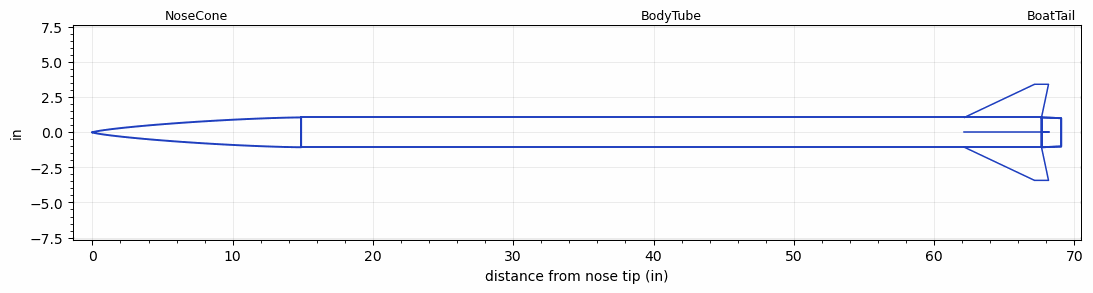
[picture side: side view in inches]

<RASAeroDocument>
 <FileVersion>2</FileVersion>
 <RocketDesign>
  <NoseCone>
   <Length>14.88</Length>
   <Diameter>2.125</Diameter>
   <Shape>Von Karman Ogive</Shape>
   <Location>0</Location>
  </NoseCone>
  <BodyTube>
   <Length>52.78</Length>
   <Diameter>2.125</Diameter>
   <Location>14.88</Location>
   <BoattailLength>1.4</BoattailLength>
   <BoattailRearDiameter>2.02</BoattailRearDiameter>
   <Fin>
    <Count>4</Count>
    <Chord>5.5</Chord>
    <Span>2.362</Span>
    <SweepDistance>5</SweepDistance>
    <TipChord>1</TipChord>
    <Thickness>0.118</Thickness>
    <LERadius>0.01</LERadius>
    <Location>5.5</Location>
    <AirfoilSection>Hexagonal</AirfoilSection>
    <FX1>0.5</FX1>
    <FX3>0.5</FX3>
   </Fin>
  </BodyTube>
  <BoatTail>
   <Length>1.4</Length>
   <Diameter>2.125</Diameter>
   <RearDiameter>2.02</RearDiameter>
   <Location>67.66</Location>
  </BoatTail>
  <Surface>Rough Camouflage Paint</Surface>
  <ModifiedBarrowman>True</ModifiedBarrowman>
  <Turbulence>True</Turbulence>
  <UseBooster1>False</UseBooster1>
  <UseBooster2>False</UseBooster2>
 </RocketDesign>
 <LaunchSite>
  <Altitude>800</Altitude>
  <Pressure>0</Pressure>
  <RodAngle>0</RodAngle>
  <RodLength>4</RodLength>
  <Temperature>50</Temperature>
  <WindSpeed>0</WindSpeed>
 </LaunchSite>
 <Recovery>
  <Altitude1>1000</Altitude1>
  <Altitude2>1000</Altitude2>
  <DeviceType1>None</DeviceType1>
  <DeviceType2>None</DeviceType2>
  <Event1>False</Event1>
  <Event2>False</Event2>
  <Size1>1</Size1>
  <Size2>1</Size2>
  <EventType1>None</EventType1>
  <EventType2>None</EventType2>
  <CD1>1.33</CD1>
  <CD2>1.33</CD2>
 </Recovery>
 <SimulationList>
  <Simulation>
   <SustainerEngine>M1378LR  (Loki)</SustainerEngine>
   <SustainerLaunchWt>11.78</SustainerLaunchWt>
   <SustainerCG>41.34</SustainerCG>
   <SustainerIgnitionDelay>0</SustainerIgnitionDelay>
   <Booster1SeparationDelay>0</Booster1SeparationDelay>
   <Booster1IgnitionDelay>0</Booster1IgnitionDelay>
   <IncludeBooster1>False</IncludeBooster1>
   <Booster2Delay>0</Booster2Delay>
   <IncludeBooster2>False</IncludeBooster2>
   <TimetoApogee>36.30991</TimetoApogee>
   <MaxAltitude>34194.67</MaxAltitude>
   <MaxVelocity>3228.88</MaxVelocity>
  </Simulation>
 </SimulationList>
</RASAeroDocument>
